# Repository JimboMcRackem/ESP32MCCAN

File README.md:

# ESP32 MCCAN

ESP32 motorcycle lighting controller. It reads the bike's CAN bus and drives 12 on/off outputs.
You configure it from a phone over its own Wi-Fi network.

The firmware is one image. `tools/embed_web.py` embeds the web app from `data/` at build time,
so there is no separate filesystem flash.

Settings and the Wi-Fi password live in NVS (namespace `mccan`). A legacy `/config.json` is
migrated once and then deleted, but only on a unit that still has the old partition table (see
below).

## Flashing over USB

Before the first USB flash of this firmware:

1. `python -m pip install cryptography` (needed by `tools/sign_update.py`).
2. `python tools/sign_update.py keygen`, then commit `src/domain/update_pubkey.h`. Firmware built
   with the all-zero placeholder key refuses every phone update until it is flashed over USB
   again.
3. Export your settings from the app's Backup tab. This firmware uses the `min_spiffs.csv`
   partition table (bigger app slots), so the old `/config.json` is not carried over. Import the
   backup after flashing.

```
PYTHONIOENCODING=utf-8 py -3.13 -m platformio run -e esp32 -t upload
```

This is the only flash. There is no `uploadfs`. Native tests run with `python -m platformio test -e native`.

The controller's Wi-Fi network is `MCCAN-XXXX` (XXXX is the last two bytes of the SoftAP MAC
address, which differs from the base MAC printed on module labels).
The default password is `mccan1234`, and the app nags until you change it.

## Releasing an update

1. Once only, before the first USB flash: `python tools/sign_update.py keygen`. The private key goes to `~/.mccan/update_key.pem`
   and the public half to `src/domain/update_pubkey.h`, which is built into the firmware.
   **Back up the key.** If it is lost, units in the field can only be updated over USB.
2. Bump `kBuildNumber` and `kVersionString` in `src/version.h`.
3. Build: `PYTHONIOENCODING=utf-8 py -3.13 -m platformio run -e esp32`
4. Sign:
   ```
   python tools/sign_update.py sign --key ~/.mccan/update_key.pem --bin .pio/build/esp32/firmware.bin --out mccan-<version>.mcup
   ```

The `.mcup` format is documented at the top of `tools/sign_update.py`.

## Installing an update from the phone

1. Join the `MCCAN-XXXX` network and open the app.
2. Go to the Device tab and choose the `.mcup` file.
3. The controller refuses an older build, and refuses any update while the bike is not parked.
4. After the update it restarts once the bike reads parked. The new image marks itself good
   after it has run for about 5 s with the Wi-Fi network up. If it crashes or is power-cycled
   before that, the next start goes back to the previous image. An image that hangs stays until
   a power cycle, and one that runs but behaves wrongly is kept: install a fixed update.

## Recovering a forgotten password

Factory reset: hold the reset button (GPIO0, labelled BOOT on the dev board) for 10 s while the
controller is running, then **release it within 5 s**. That erases the settings, and the
controller restarts with defaults (password `mccan1234`) as soon as the bike reads parked. A short
press does nothing. If the button is still held 5 s after the 10 s mark, the reset is cancelled;
release it and start a new 10 s hold to try again. The lamps keep working throughout.

Feedback: on the MCCAN board the status LED (GPIO13) fast-blinks at the 10 s mark (release now),
goes solid once the settings are erased, and goes off if cancelled. The dev board has no LED on
GPIO13: watch the serial log instead (`reset button held 10 s: release within 5 s ...`,
`factory reset: settings erased`).

Holding the button at power-up enters the ESP32's USB flashing mode instead. That is harmless.

## Bring-up notes

- On the dev board, a serial terminal that asserts DTR without RTS can hold GPIO0 low through the
  auto-program circuit. Held, it arms the reset at 10 s and cancels it at 15 s; it never erases
  unless the line is released inside that window. Use a monitor that leaves DTR and RTS
  deasserted.
- Hold BOOT through "Connecting......" if the upload cannot connect.

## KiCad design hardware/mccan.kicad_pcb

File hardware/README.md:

# MCCAN Hardware

This is the KiCad 10.0.2 project for the ESP32 MCCAN lighting controller. The board is the
**plan4 board**: 140 × 100 mm, 8 layers, assembled by JLCPCB.

- Schematic spec: `../docs/superpowers/specs/2026-10-17-emarked-module-redesign-design.md`. The
  aux stage has its own spec: `../docs/superpowers/specs/2026-11-13-aux-stage-design.md`.
- Layout spec: `../docs/superpowers/specs/2026-11-13-board-layout-phase-b-design.md`.
- Ordering is in **`docs/fabrication.md`**, the harness in `docs/harness.md`, and routing in
  `docs/routing-tool.md`.

Everything here is generated by `scripts/`. Never hand-edit a `.kicad_sch`, `.kicad_pcb`,
`.kicad_pro` or `.kicad_dru`.

## kicad-cli is not on PATH

Bash:       "/c/Program Files/KiCad/10.0/bin/kicad-cli.exe" <args>
PowerShell: & "C:\Program Files\KiCad\10.0\bin\kicad-cli.exe" <args>

On Windows, set `PYTHONIOENCODING=utf-8`, because several scripts print non-ASCII.

## Board status (phase B, 2026-11-14)

**The board is ready to order.**

- DRC is clean at every severity.
- The JLCPCB package is generated and checked.
- Every BOM line is in stock. U10 relies on owner-approved global sourcing, and L2 (11 in
  stock against 10) is approved for it if it runs short.

See "Last full run" below for the evidence.

- **Outline: 140 × 100 mm, 1 mm corner radius, M3 holes 5 mm in from each corner.**
  - The board fits because the eight wire tails go in one row on the bottom (cable) edge. Their
    courtyards total 122.2 mm, against 123.1 mm between the courtyards of the bottom mounting
    holes.
  - U5 sits on the opposite (top) edge. Its antenna overhangs the edge, and the antenna keep-out
    is clear on every layer.
  - Regions, left to right (`scripts/layout_pcb.py`):
    - feed A input and filter;
    - rails;
    - outputs (U11–U13), with test-pad bank 1;
    - MCU and CAN;
    - feed B and the aux stage (Q13/Q14, U14), with bank 2.
- **Stackup: 8 layers, 1.6 mm, 1 oz on every layer.**
  - Signals run on F.Cu, In2, In5 and B.Cu.
  - GND planes are on In1, In4 and In6, with GND_IN and GND_B islands.
  - In3 is power (VBAT, VBAT_B).
  - Feed B's 6.4 A runs on FEED_B_P pours on F.Cu, In5 and B.Cu.
  - There is no controlled impedance.
- **Assembly:** single-sided, top only, with every part placed by JLCPCB. The only THT parts are
  J2 and L2.
- **J2 (programming header) is fitted by JLCPCB, not left DNP.** L2 needs THT service anyway, and
  bring-up flashes the board over J2. J2 is reachable only with the lid off, as are SW1 and SW2
  beside it. Normal updates go over WiFi (signed OTA).
- **Test pads:** 30 bare SMD pads (TP1–TP30), each labelled with its net name on the silkscreen.
  They are in two banks plus TP30 (GND_IN), and every bank is within clip reach of a GND pad. They
  are not in the BOM.
- **Cables:** one row on the bottom edge, through seven glands (`docs/harness.md` §2).

### Before ordering

1. Re-run the stock check on the day of the order: `python scripts/check_stock.py`. It exits 1 on
   any SHORT or MISSING line. Use `--boards N` for a different quantity.
2. Follow `docs/fabrication.md` §8:
   - confirm **every** row of `output/jlcpcb/rotation-review.txt` (39 parts) in JLCPCB's
     placement preview: no rotation offset has been checked against JLCPCB;
   - read JLCPCB's DFM report.

### Open items

These change values only; the footprints stay.

- **R82–R85**, the yellow series resistors, wait on bench measurements.
- **The blue pod wire (J10.4, J11.4)** is not connected. It waits until its role is measured.
  Keep the pad.
- The fuse ratings and aux circuit ratings must be confirmed on the bike (`docs/harness.md`).

## Verification gates, in run order

Run from `hardware/`, with `K="/c/Program Files/KiCad/10.0/bin/kicad-cli.exe"`:

```
# 1. schematic
python scripts/gen_root.py && python scripts/gen_power_input.py && python scripts/gen_rails.py \
  && python scripts/gen_mcu_can.py && python scripts/gen_outputs.py
"$K" sch export netlist --format kicadsexpr -o output/netlist.net mccan.kicad_sch
"$K" sch erc --severity-error --exit-code-violations -o output/erc.rpt mccan.kicad_sch
python scripts/check_netlist.py

# 2. board (routes come frozen from scripts/routes_signal.json; see docs/routing-tool.md)
python scripts/gen_pcb.py && python scripts/gen_netclasses.py
"$K" pcb drc --severity-all --schematic-parity --refill-zones --exit-code-violations \
  -o output/drc.rpt mccan.kicad_pcb
ok=1; for c in frame placement antenna courtyards grounds zone_islands power_paths \
                plane_width plane_mincut vias geometry; do python scripts/check_$c.py || ok=0; done
python scripts/test_check_plane_mincut.py || ok=0; [ $ok = 1 ]

# 3. fabrication
python scripts/gen_fab.py && python scripts/gen_fab.py --check && python scripts/check_stock.py
```

**DRC must use `--refill-zones`.** Without it, every pad welded to a pour reads as unconnected.

**DRC must run at `--severity-all`.** `--severity-error` discards every rule set to `warning`:
silk, text and library metadata. `gen_netclasses.py` promotes the seven rules that can fail this
board's copper to `error` (`SEVERITIES`). But if a KiCad upgrade adds a rule that defaults to
`warning`, an error-only run would never see it.

The accepted residual is **zero**: 0 violations, 0 unconnected and 0 parity issues, at every
severity. With `--exit-code-violations`, any finding exits 5.

`check_plane_mincut.py` (about a minute) measures each power path's narrowest copper by max-flow
/ min-cut on a 0.1 mm raster, so it finds a neck at any angle. `check_plane_width.py` only cuts
along rows and columns, which can pass a diagonally necked pour; keep it as the fast first look.

`check_density.py` reports how full each region is. It is informational, not a gate.

### Last full run (2026-11-15, robustness changes: U10 ON tie, D25 SMBJ18A, ILIM 56.2 k, J2 silk)

| Step | Result |
|---|---|
| Schematic generators | `power_input` and `outputs` changed as intended; the other sheets byte-identical |
| Netlist diff vs 2026-11-14 | U10.9 joins `VCC10`; D25 SMBJ18A; R62-R64 56.2k; nothing else |
| ERC | 0 violations |
| `check_netlist.py`, `verify_fpmap.py` | every group PASS; 0 failures |
| `gen_pcb.py` | exit 0 (hand routes clear); 2137 frozen segments, 504 router vias, plus the ON track |
| DRC, all severities, parity | **0 violations, 0 unconnected, 0 parity issues** |
| `check_frame`, `placement`, `antenna`, `courtyards`, `grounds`, `zone_islands`, `power_paths`, `plane_width`, `plane_mincut`, `vias`, `geometry`, `test_check_plane_mincut` | PASS |
| `gen_fab.py --check` | PASS: 39 orientation-checked parts (13 recalled, 26 unverified; none confirmed) |
| `check_stock.py --boards 5` | exit 0. U10 (LTC4380) GLOBAL as before (owner-approved); L2 11 for 10 |

## Board setup decisions

**Minimum track width and minimum connection width are both 0.15 mm, and they are tied on
purpose.** `min_connection` is the narrowest copper that may carry a connection. If it were set
above the thinnest legal track, every legitimately necked track would violate a rule that the same
file grants. Only the GND planes may neck further, to 0.12 mm between via antipads, through a
scoped rule in `mccan.kicad_dru` (`scripts/gen_netclasses.py`, `PLANE_NECK_RULE`).

**Reference designators are on F.Fab, except J\*, F\*, U\*, Q\*, D\* and L\*.**

- Test pads are identified on the silkscreen by their **net name** instead (`gen_pcb.tp_labels`).
- `gen_pcb.silk_refs` places each kept designator clear of every pad, of every other part's silk,
  of its own outline and of the board edge.
- Values are on F.Fab, so `output/jlcpcb/assembly.pdf` is a fully labelled copy.

## Sheet responsibilities

| Sheet | Contents |
|---|---|
| power_input | Feed A (J1): LTC4380 U10 surge stopper with Q10/Q11 (no board fuse; the fuse is in the harness), 24 V TVS, pi + CM filter -> `VBAT`. Feed B (J9): SQJ461EP P-FET Q13 for reverse polarity, 15 V gate zener D24, SMBJ18A TVS D25 (29.2 V clamp, inside U14's 35 V) -> `VBAT_B`, no filter, no LTC4380. `GND_B` (also the pods' return, out to the outputs sheet) meets `GND_IN` (the connector side of choke L2) only at net-tie NT1, so neither feed's return current bypasses L2's return winding |
| rails | Low-Iq buck -> `+3V3_ALW`, gated `+5V` (`EN_5V`). No boost and no `+3V3_SW` |
| mcu_can | ESP32-WROOM-32E, TJA1042T/3 (listen-only, TXD pulled up, no MCU link), programming header, 4.7 k series resistors on the diagnostic lines. GPIO 13 is `AUX_PWM` (left pod yellow; the status LED is gone, 2026-11-13) and GPIO 12 is `AUX_PWM_R` (right pod yellow, 2026-11-21) |
| outputs | Three TPS4HC120A-Q1 quads U11-U13 (TPS4H160B until 2026-11-13, no stock) (D1: 12 channels, 10 used, 2 spare), harness tails J3 (front, 5), J4 + J5 (rear, 4 + 3), CAN tail J8. Aux stage (2026-11-13): BTS7008-2EPA U14 switches both pods from `VBAT_B`, 74AHCT1G126GV U15 (left) buffers `AUX_PWM` and U16 (right) buffers `AUX_PWM_R` to its yellow (enabled only while that pod is powered), pod tails J10/J11. See `docs/superpowers/specs/2026-11-13-aux-stage-design.md` |

The pin map and net names are the generators' (`scripts/gen_*.py`, `scripts/quadpins.py`) and the
netlist `output/netlist.net`. The plan3 pin tables that used to be here (PCA9685, mux, ignition
sense, PWM nets) described a board that no longer exists and have been removed.

### ESP32 pin rules that still hold

- GPIO 6-11 are the module's flash and are unusable. GPIO 37 and 38 are not bonded out.
- GPIO 34-39 are input-only and have **no internal pulls**. Here: 34 `SNS_A`, 35 `CAN_RXD`
  (RTC, EXT1 wake), 36 `SNS_B`, 39 `SNS_C`.
- ADC2 fails while Wi-Fi is up, so the sense inputs are all ADC1.
- Strapping pins, and what this board ties them to:
  - GPIO 0 is `BOOT_N`: the BOOT button SW1 and the auto-reset transistor Q3.
  - GPIO 2 is `DIAG_EN`: 4.7 k series, with R33 47 k pull-down on the chip side. It must be low
    for download, and the same pull-down holds the switches' `DIAG_EN` low. High level: 47 k ∥ 33.3 k
    (three chips at 100 k min) = 19.5 k, so 3.3 × 19.5 / (19.5 + 4.7) = 2.66 V against VIH 2.0 V.
  - GPIO 5 and 15 are `DIAG_SEL0` / `DIAG_SEL1`: 4.7 k series, **no pull** (their level is
    irrelevant while `DIAG_EN` is low). The three SEH internal pull-downs (100 k min each) load
    GPIO 15 against its internal pull-up, so the ROM boot log will probably be muted; that is
    harmless. Optional fix: a 10 k pull-up on the MCU side of R32 (not fitted).
  - GPIO 12 is `AUX_PWM_R`, the right pod's yellow PWM to U16 (2026-11-21), with R36 10 k to GND
    (flash voltage select, and the buffer input's pull-down). It is also the firmware's nominal TWAI
    TX pin: `CanBus::begin` hands it back to input + pull-down once TWAI starts, and only then does
    the firmware attach the right pod's LEDC channel. It must never be driven high through a reset.
- No lamp output sits on a strapping pin or on GPIO 14.

### Layout notes (honoured by the plan4 layout)

- **U10 (LTC4380) `ON` is tied to `VCC10`** (2026-11-15). It used to be left open on its internal
  1 Mohm pull-up, which needs < 1 uA leakage to ground: about 400 kOhm of moisture or flux would
  have held the whole board off. A 0.15 mm F.Cu track runs from pad 9 under the body to `VCC10`'s
  via. The old In1 keep-out and `check_power_paths` guard stay as belt-and-braces.
- `NT1` is the deliberate `GND_B` / `GND_IN` star point (connector side of L2, so no return current bypasses L2's return winding); place it deliberately (spec §4.1.1). It is a 2.0 mm tie so it outlasts the harness fuse when one feed is reversed while the other is connected.

### Bring-up checklist

- **ROM boot log may be absent.** The three SEH internal pull-downs load GPIO 15 (MTDO), so the boot ROM log is probably muted. Harmless. Optional fix: a 10 k pull-up on the MCU side of R32 (not fitted).
- **GPIO12 / flash voltage.** The TWAI driver needs a TX pin and drives it high; on this board that is GPIO12, the MTDI strap. Since 2026-11-15 `CanBus::begin` returns GPIO12 to input + pull-down right after `twai_start()` (listen-only never transmits), and R36 holds it low at every reset. Since 2026-11-21 GPIO12 is also `AUX_PWM_R`, the right pod's yellow PWM, attached only after `CanBus::begin`. Check on the bench: GPIO12 reads ~0 V while running with the right pod off, carries the pod PWM when it is on, and CAN frames still arrive. The optional permanent remedy is `espefuse.py set_flash_voltage 3.3V`, which is **IRREVERSIBLE** and is the owner's decision; it has not been run.
- **Diagnostics settling.** After any `DIAG_SEL` or `DIAG_EN` change wait >= 400 us before reading `SNS_x`.
- **Reverse polarity.** Test one feed reversed with the other disconnected, and the whole harness reversed. Test one feed reversed with the other connected only on a current-limited bench supply: that drives fault current through NT1 and the shared return until the harness fuse clears.
- `R100` (33 mOhm) sets feed A's limit at 1.36-1.67 A, between its ~0.87 A load and its ~2 A fuse (aux spec A10). Re-check it against the measured start-up current.
- **Shorted lamp vs feed A's limit.** The quads' ILIM is 0.25 A (R62-R64 56.2 k, since 2026-11-15; was 0.5 A). The MCU's rail is behind U10, so one short at 0.5 A (peaking 1.4x) on top of the 0.87 A worst case could reach U10's limit and reset the MCU in a loop. At 0.25 A a single short stays under it (~1.24 A) and that channel latches off. Check on a current-limited bench supply: with all lamps on, short one output to GND; the board must stay up and only that channel go dark. Two simultaneous shorts can still trip U10.
- **J2 is not an FTDI header.** Pin order 3V3 GND TX RX DTR RTS (labelled on the silk). A generic FTDI cable (GND CTS VCC TX RX RTS) puts GND on +3V3_ALW and 5 V on TXD0. Use the MCCAN programmer.

Plan3 history (the 200 × 140 mm PCBWay board, the RGB output stage, Task 1 status) is in git history and `archive/`.

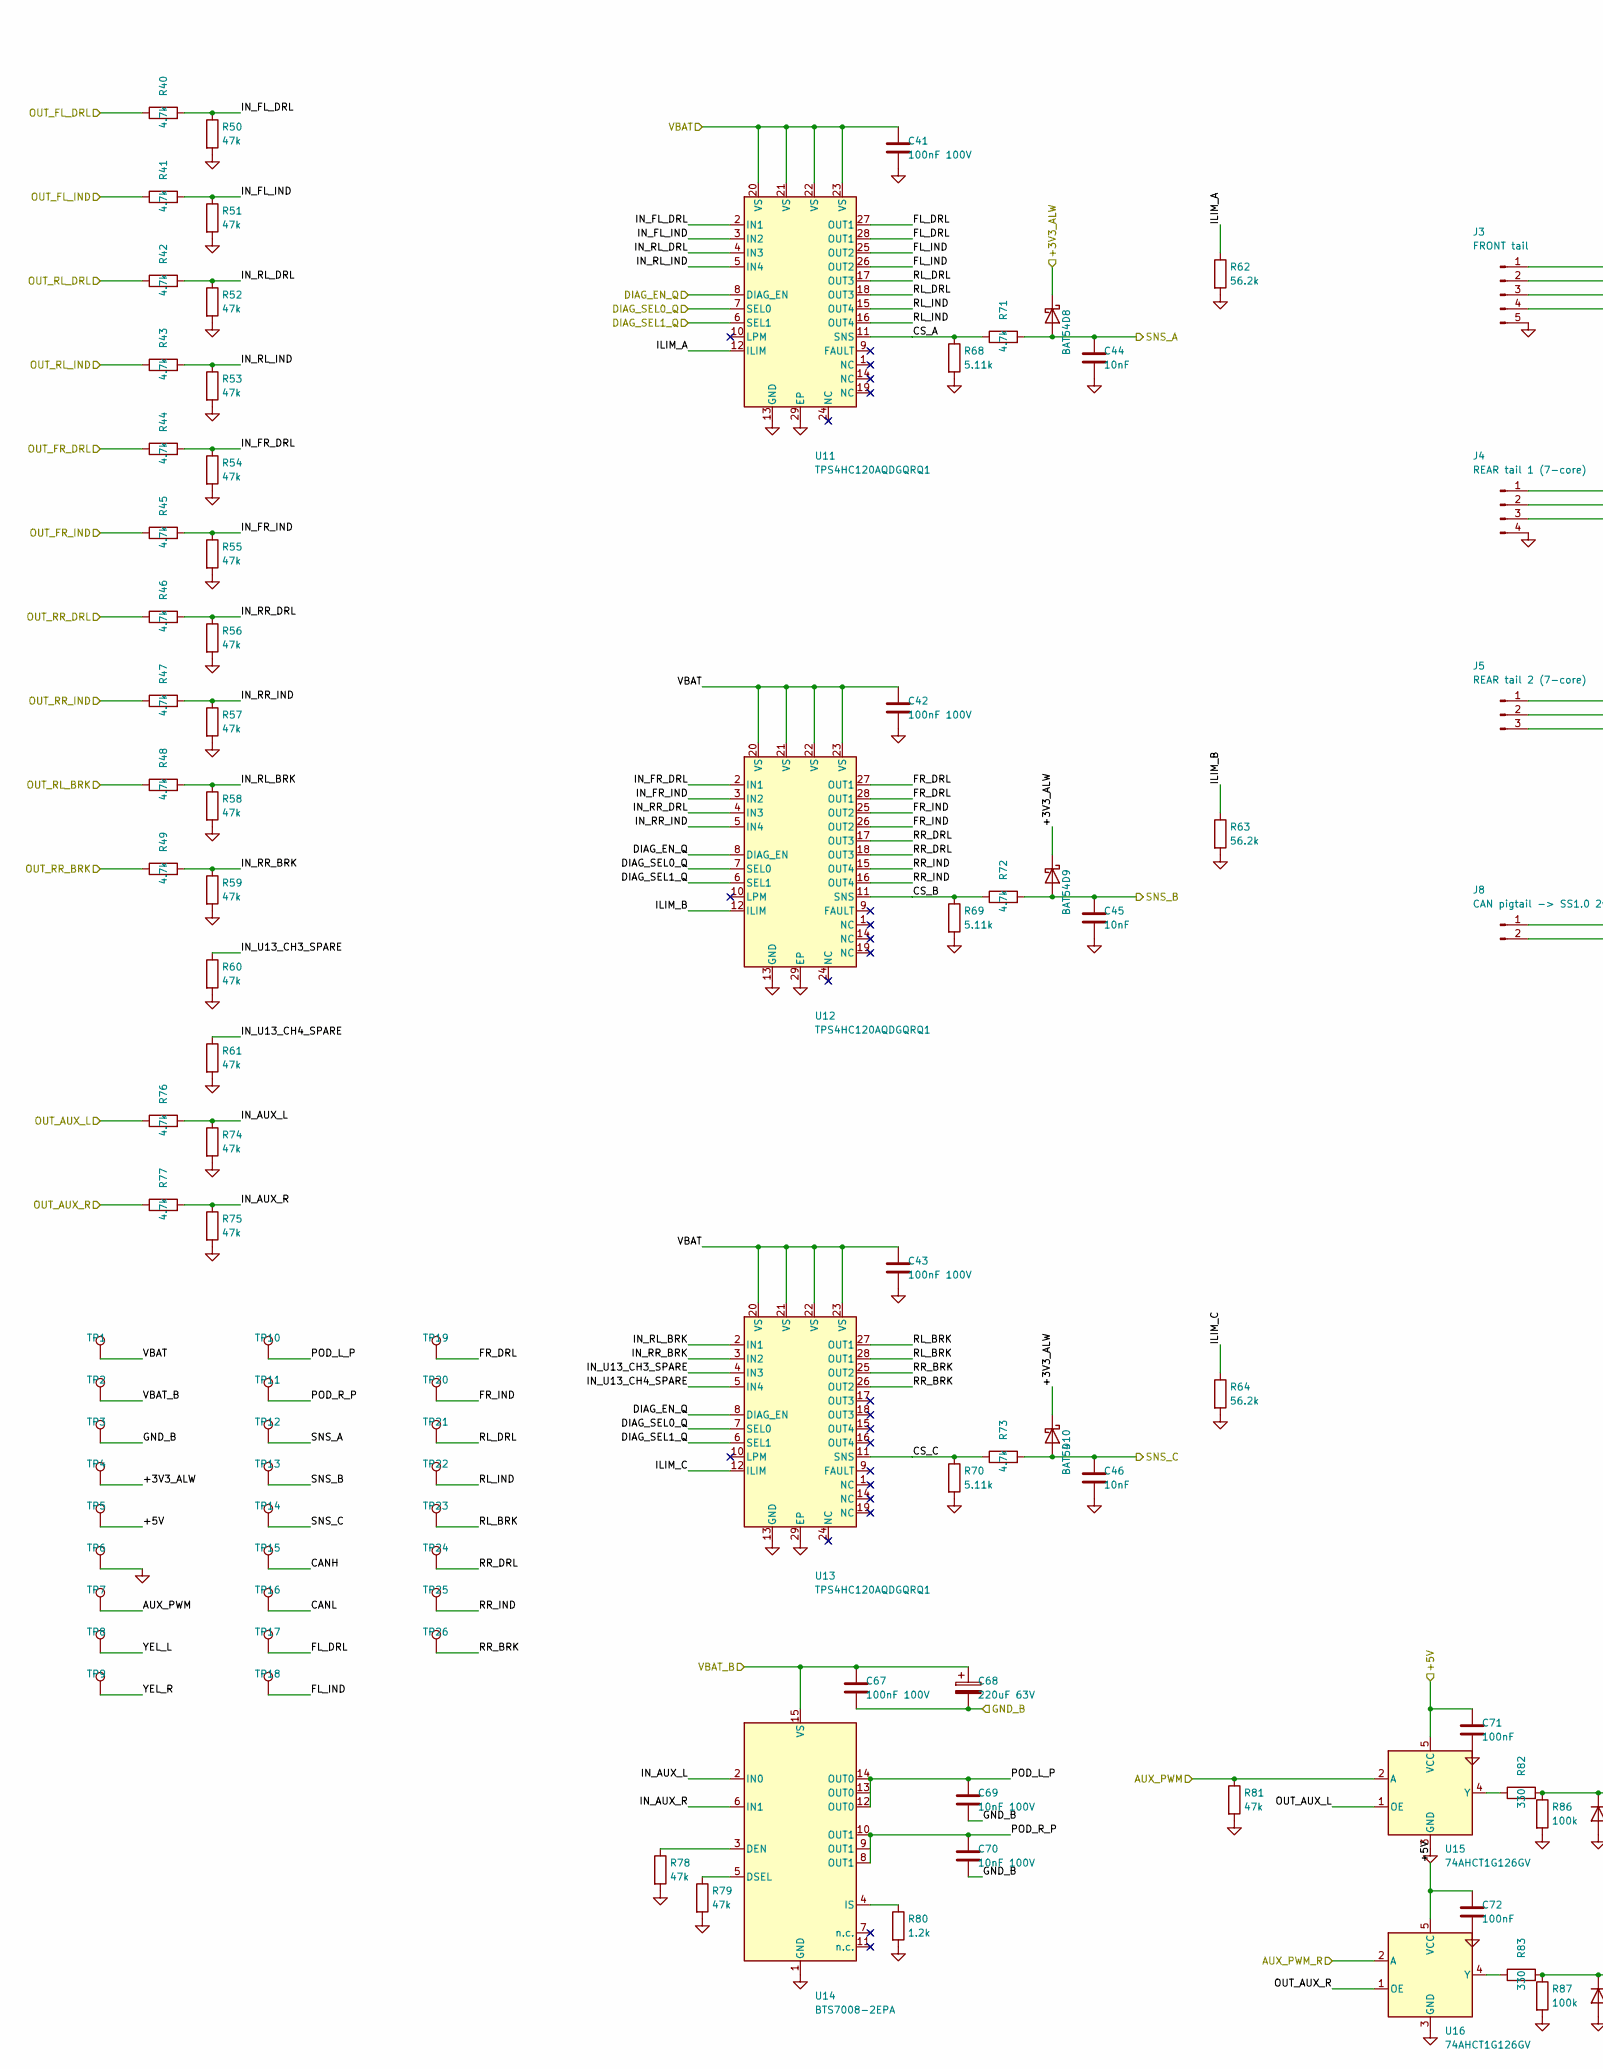
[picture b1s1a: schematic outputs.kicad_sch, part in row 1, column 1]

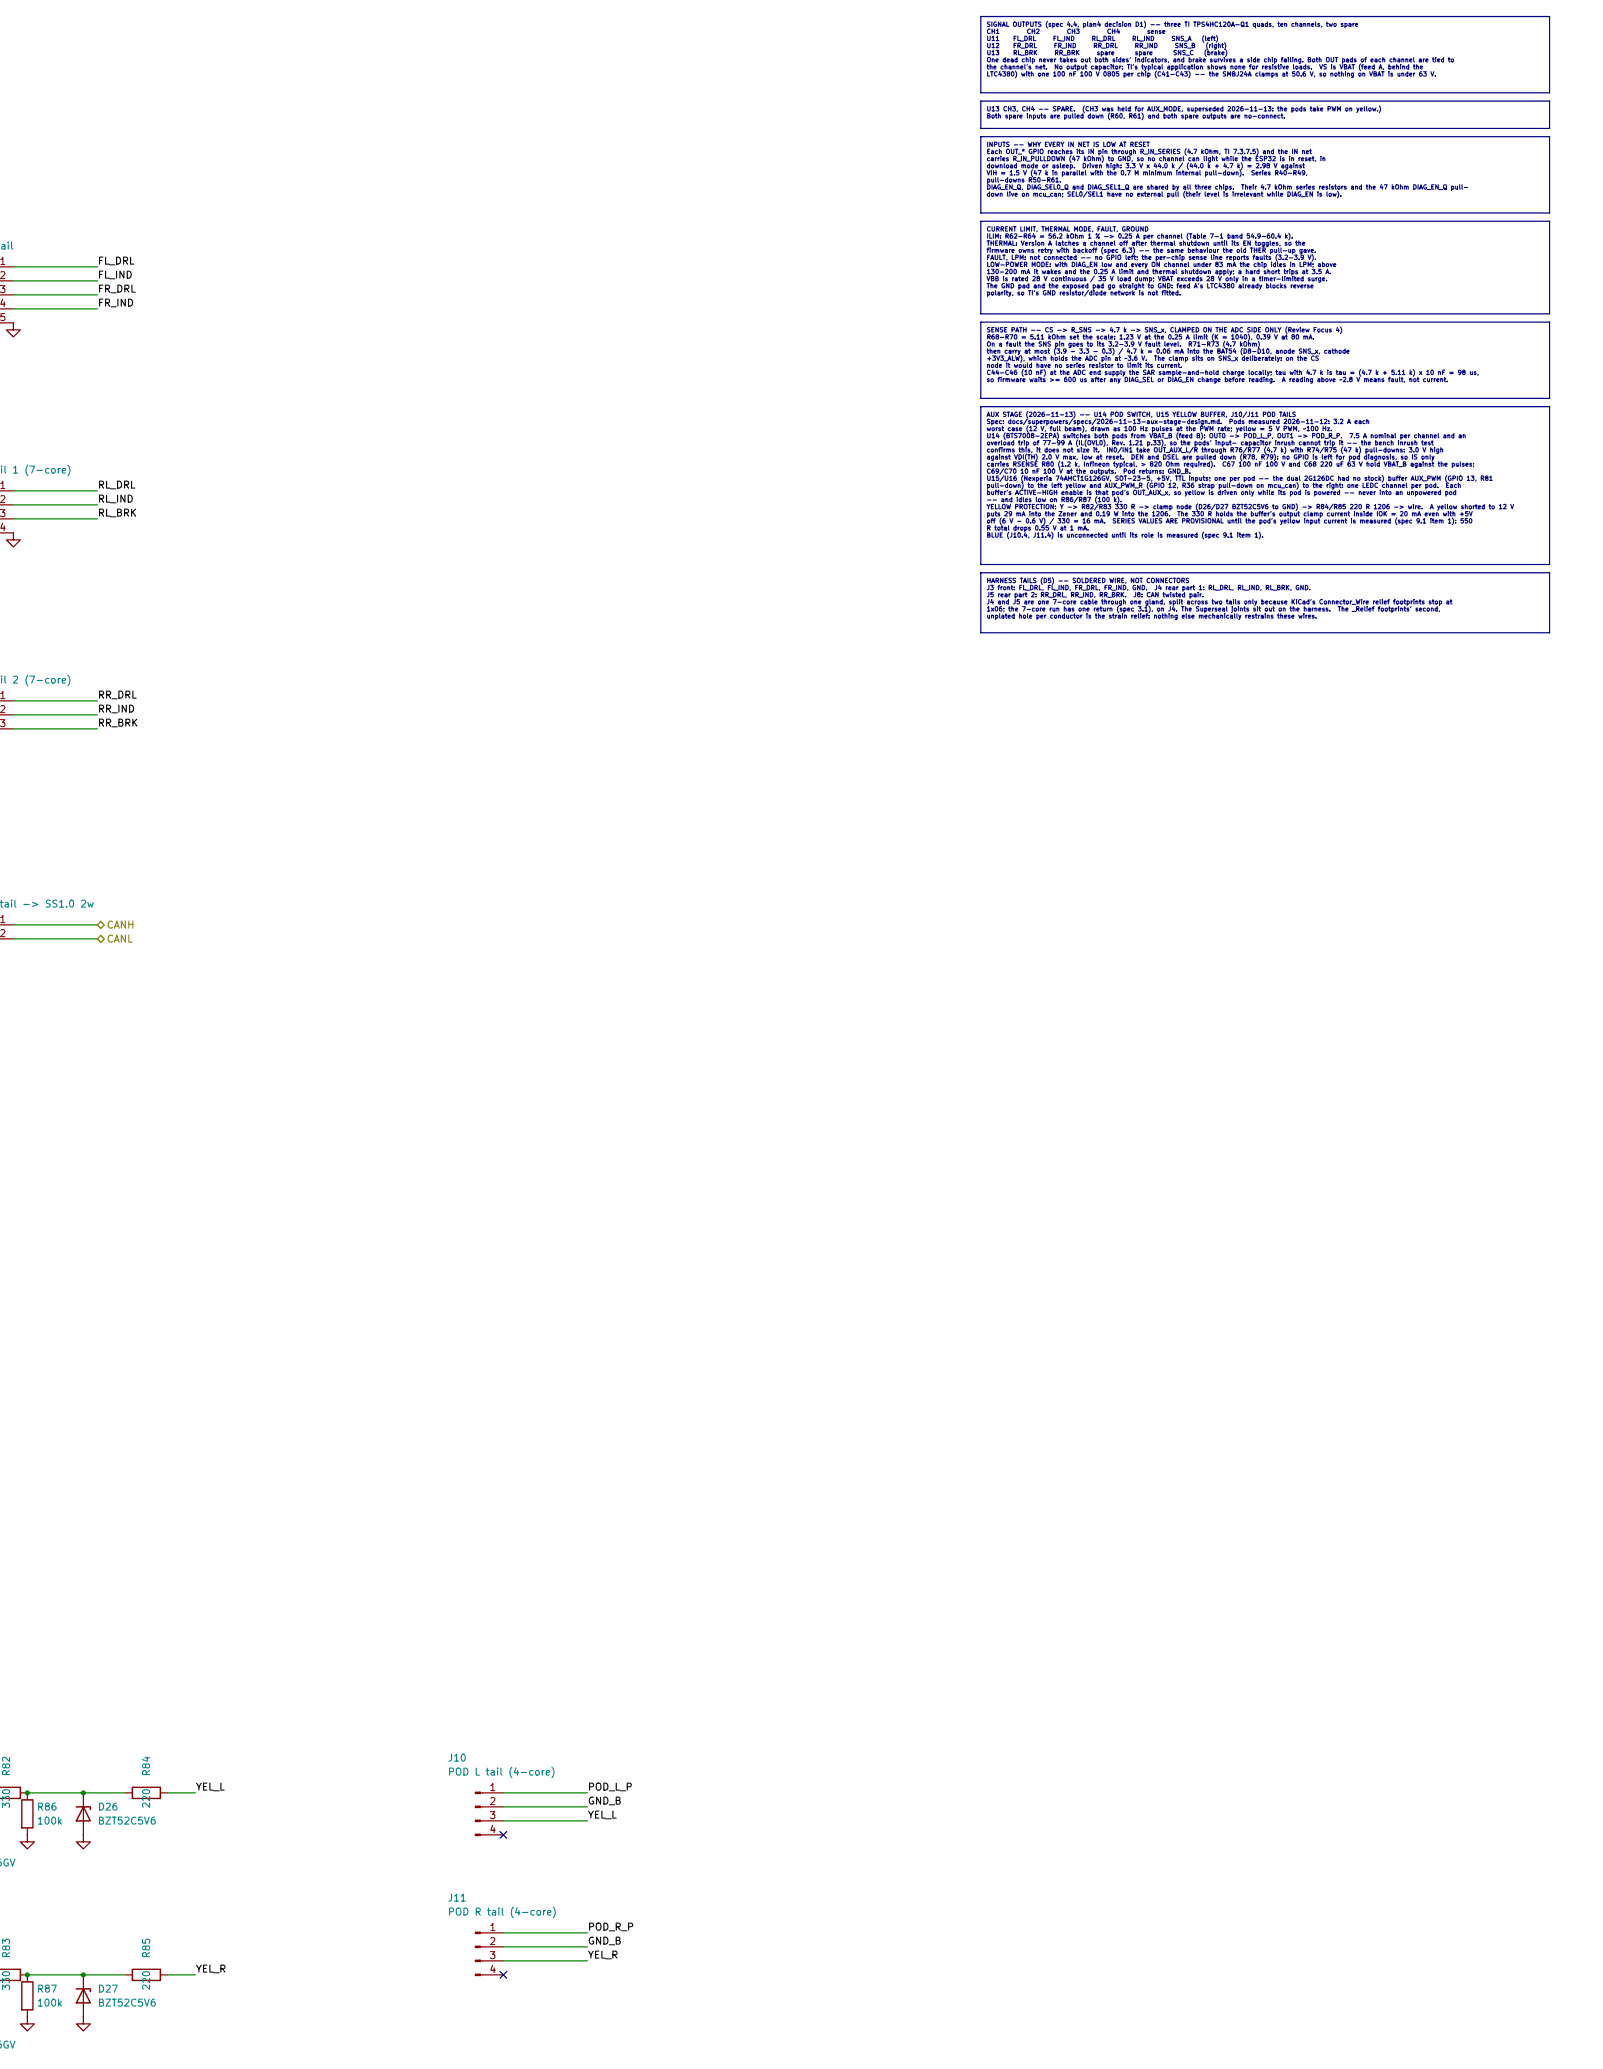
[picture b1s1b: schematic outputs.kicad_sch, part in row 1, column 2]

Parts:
C41, C42, C43, C67: 100nF 100V; C_0805_2012Metric
C44, C45, C46: 10nF; C_0603_1608Metric
C68: 220uF 63V; CP_Elec_10x10.5
C69, C70: 10nF 100V; C_0805_2012Metric
C71, C72: 100nF; C_0603_1608Metric
D8, D9, D10: BAT54; D_SOD-123
D26, D27: BZT52C5V6; D_SOD-123
J3: FRONT tail; SolderWire-0.5sqmm_1x05_P4.6mm_D0.9mm_OD2.1mm_Relief
J4: REAR tail 1 (7-core); SolderWire-0.5sqmm_1x04_P4.6mm_D0.9mm_OD2.1mm_Relief
J5: REAR tail 2 (7-core); SolderWire-0.5sqmm_1x03_P4.6mm_D0.9mm_OD2.1mm_Relief
J8: CAN pigtail -> SS1.0 2w; SolderWire-0.5sqmm_1x02_P4.6mm_D0.9mm_OD2.1mm_Relief
J10: POD L tail (4-core); SolderWire-1sqmm_1x04_P5.4mm_D1.4mm_OD2.7mm_Relief
J11: POD R tail (4-core); SolderWire-1sqmm_1x04_P5.4mm_D1.4mm_OD2.7mm_Relief
R40, R41, R42, R43, R44, R45, R46, R47, R48, R49, R71, R72, R73, R76, R77: 4.7k; R_0603_1608Metric
R50, R51, R52, R53, R54, R55, R56, R57, R58, R59, R60, R61, R74, R75, R78, R79, R81: 47k; R_0603_1608Metric
R62, R63, R64: 56.2k; R_0603_1608Metric
R68, R69, R70: 5.11k; R_0603_1608Metric
R80: 1.2k; R_0603_1608Metric
R82, R83: 330; R_0603_1608Metric
R84, R85: 220; R_1206_3216Metric
R86, R87: 100k; R_0603_1608Metric
TP1: VBAT; TestPoint_Pad_D1.5mm
TP2: VBAT_B; TestPoint_Pad_D1.5mm
TP3: GND_B; TestPoint_Pad_D1.5mm
TP4: +3V3_ALW; TestPoint_Pad_D1.5mm
TP5: +5V; TestPoint_Pad_D1.5mm
TP6: GND; TestPoint_Pad_D1.5mm
TP7: AUX_PWM; TestPoint_Pad_D1.5mm
TP8: YEL_L; TestPoint_Pad_D1.5mm
TP9: YEL_R; TestPoint_Pad_D1.5mm
TP10: POD_L_P; TestPoint_Pad_D1.5mm
TP11: POD_R_P; TestPoint_Pad_D1.5mm
TP12: SNS_A; TestPoint_Pad_D1.5mm
TP13: SNS_B; TestPoint_Pad_D1.5mm
TP14: SNS_C; TestPoint_Pad_D1.5mm
TP15: CANH; TestPoint_Pad_D1.5mm
TP16: CANL; TestPoint_Pad_D1.5mm
TP17: FL_DRL; TestPoint_Pad_D1.5mm
TP18: FL_IND; TestPoint_Pad_D1.5mm
TP19: FR_DRL; TestPoint_Pad_D1.5mm
TP20: FR_IND; TestPoint_Pad_D1.5mm
TP21: RL_DRL; TestPoint_Pad_D1.5mm
TP22: RL_IND; TestPoint_Pad_D1.5mm
TP23: RL_BRK; TestPoint_Pad_D1.5mm
TP24: RR_DRL; TestPoint_Pad_D1.5mm
TP25: RR_IND; TestPoint_Pad_D1.5mm
TP26: RR_BRK; TestPoint_Pad_D1.5mm
U11, U12, U13: TPS4HC120AQDGQRQ1; TI_DGQ0028C
U14: BTS7008-2EPA; Infineon_PG-TSDSO-14-22
U15, U16: 74AHCT1G126GV; SOT-23-5

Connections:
/+3V3_ALW: D8.1 (K), D9.1 (K), D10.1 (K), TP4.1; also elsewhere on the board
/+5V: C71.1, C72.1, TP5.1, U15.5 (VCC), U16.5 (VCC); also elsewhere on the board
/AUX_PWM: R81.1, TP7.1, U15.2 (A); also elsewhere on the board
/AUX_PWM_R: U16.2 (A); also elsewhere on the board
/CANH: J8.1, TP15.1; also elsewhere on the board
/CANL: J8.2, TP16.1; also elsewhere on the board
/DIAG_EN_Q: U11.8 (DIAG_EN), U12.8 (DIAG_EN), U13.8 (DIAG_EN); also elsewhere on the board
/DIAG_SEL0_Q: U11.7 (SEL0), U12.7 (SEL0), U13.7 (SEL0); also elsewhere on the board
/DIAG_SEL1_Q: U11.6 (SEL1), U12.6 (SEL1), U13.6 (SEL1); also elsewhere on the board
/GND_B: C67.2, C68.2, C69.2, C70.2, J10.2, J11.2, TP3.1; also elsewhere on the board
/OUT_AUX_L: R76.1, U15.1 (OE); also elsewhere on the board
/OUT_AUX_R: R77.1, U16.1 (OE); also elsewhere on the board
/OUT_FL_DRL: R40.1; also elsewhere on the board
/OUT_FL_IND: R41.1; also elsewhere on the board
/OUT_FR_DRL: R44.1; also elsewhere on the board
/OUT_FR_IND: R45.1; also elsewhere on the board
/OUT_RL_BRK: R48.1; also elsewhere on the board
/OUT_RL_DRL: R42.1; also elsewhere on the board
/OUT_RL_IND: R43.1; also elsewhere on the board
/OUT_RR_BRK: R49.1; also elsewhere on the board
/OUT_RR_DRL: R46.1; also elsewhere on the board
/OUT_RR_IND: R47.1; also elsewhere on the board
/SNS_A: C44.1, D8.2 (A), R71.2, TP12.1; also elsewhere on the board
/SNS_B: C45.1, D9.2 (A), R72.2, TP13.1; also elsewhere on the board
/SNS_C: C46.1, D10.2 (A), R73.2, TP14.1; also elsewhere on the board
/VBAT: C41.1, C42.1, C43.1, TP1.1, U11.20 (VS), U11.21 (VS), U11.22 (VS), U11.23 (VS), U12.20 (VS), U12.21 (VS), U12.22 (VS), U12.23 (VS), U13.20 (VS), U13.21 (VS), U13.22 (VS), U13.23 (VS); also elsewhere on the board
/VBAT_B: C67.1, C68.1, TP2.1, U14.15 (VS); also elsewhere on the board
/outputs/CS_A: R68.1, R71.1, U11.11 (SNS)
/outputs/CS_B: R69.1, R72.1, U12.11 (SNS)
/outputs/CS_C: R70.1, R73.1, U13.11 (SNS)
/outputs/FL_DRL: J3.1, TP17.1, U11.27 (OUT1), U11.28 (OUT1)
/outputs/FL_IND: J3.2, TP18.1, U11.25 (OUT2), U11.26 (OUT2)
/outputs/FR_DRL: J3.3, TP19.1, U12.27 (OUT1), U12.28 (OUT1)
/outputs/FR_IND: J3.4, TP20.1, U12.25 (OUT2), U12.26 (OUT2)
/outputs/ILIM_A: R62.1, U11.12 (ILIM)
/outputs/ILIM_B: R63.1, U12.12 (ILIM)
/outputs/ILIM_C: R64.1, U13.12 (ILIM)
/outputs/IN_AUX_L: R74.1, R76.2, U14.2 (IN0)
/outputs/IN_AUX_R: R75.1, R77.2, U14.6 (IN1)
/outputs/IN_FL_DRL: R40.2, R50.1, U11.2 (IN1)
/outputs/IN_FL_IND: R41.2, R51.1, U11.3 (IN2)
/outputs/IN_FR_DRL: R44.2, R54.1, U12.2 (IN1)
/outputs/IN_FR_IND: R45.2, R55.1, U12.3 (IN2)
/outputs/IN_RL_BRK: R48.2, R58.1, U13.2 (IN1)
/outputs/IN_RL_DRL: R42.2, R52.1, U11.4 (IN3)
/outputs/IN_RL_IND: R43.2, R53.1, U11.5 (IN4)
/outputs/IN_RR_BRK: R49.2, R59.1, U13.3 (IN2)
/outputs/IN_RR_DRL: R46.2, R56.1, U12.4 (IN3)
/outputs/IN_RR_IND: R47.2, R57.1, U12.5 (IN4)
/outputs/IN_U13_CH3_SPARE: R60.1, U13.4 (IN3)
/outputs/IN_U13_CH4_SPARE: R61.1, U13.5 (IN4)
/outputs/POD_L_P: C69.1, J10.1, TP10.1, U14.12 (OUT0), U14.13 (OUT0), U14.14 (OUT0)
/outputs/POD_R_P: C70.1, J11.1, TP11.1, U14.8 (OUT1), U14.9 (OUT1), U14.10 (OUT1)
/outputs/RL_BRK: J4.3, TP23.1, U13.27 (OUT1), U13.28 (OUT1)
/outputs/RL_DRL: J4.1, TP21.1, U11.17 (OUT3), U11.18 (OUT3)
/outputs/RL_IND: J4.2, TP22.1, U11.15 (OUT4), U11.16 (OUT4)
/outputs/RR_BRK: J5.3, TP26.1, U13.25 (OUT2), U13.26 (OUT2)
/outputs/RR_DRL: J5.1, TP24.1, U12.17 (OUT3), U12.18 (OUT3)
/outputs/RR_IND: J5.2, TP25.1, U12.15 (OUT4), U12.16 (OUT4)
/outputs/YEL_L: J10.3, R84.2, TP8.1
/outputs/YEL_R: J11.3, R85.2, TP9.1
GND: C41.2, C42.2, C43.2, C44.2, C45.2, C46.2, C71.2, C72.2, D26.2 (A), D27.2 (A), J3.5, J4.4, R50.2, R51.2, R52.2, R53.2, R54.2, R55.2, R56.2, R57.2, R58.2, R59.2, R60.2, R61.2, R62.2, R63.2, R64.2, R68.2, R69.2, R70.2, R74.2, R75.2, R78.2, R79.2, R80.2, R81.2, R86.2, R87.2, TP6.1, U11.13 (GND), U11.29 (EP), U12.13 (GND), U12.29 (EP), U13.13 (GND), U13.29 (EP), U14.1 (GND), U15.3 (GND), U16.3 (GND); also elsewhere on the board
unnamed: D26.1 (K), R82.2, R84.1, R86.1
unnamed: D27.1 (K), R83.2, R85.1, R87.1
unnamed: R78.1, U14.3 (DEN)
unnamed: R79.1, U14.5 (DSEL)
unnamed: R80.1, U14.4 (IS)
unnamed: R82.1, U15.4 (Y)
unnamed: R83.1, U16.4 (Y)

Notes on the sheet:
SENSE PATH -- CS -> R_SNS -> 4.7 k -> SNS_x, CLAMPED ON THE ADC SIDE ONLY (Review Focus 4) R68-R70 = 5.11 kOhm set the scale: 1.23 V at the 0.25 A limit (K = 1040), 0.39 V at 80 mA. On a fault the SNS pin goes to its 3.2-3.9 V fault level. R71-R73 (4.7 kOhm) then carry at most (3.9 - 3.3 - 0.3) / 4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
CURRENT LIMIT, THERMAL MODE, FAULT, GROUND ILIM: R62-R64 = 56.2 kOhm 1 % -> 0.25 A per channel (Table 7-1 band 54.9-60.4 k). THERMAL: Version A latches a channel off after thermal shutdown until its EN toggles, so the firmware owns retry with backoff (spec 6.3) -- the same behaviour the old THER pu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
AUX STAGE (2026-11-13) -- U14 POD SWITCH, U15 YELLOW BUFFER, J10/J11 POD TAILS Spec: docs/superpowers/specs/2026-11-13-aux-stage-design.md. Pods measured 2026-11-12: 3.2 A each worst case (12 V, full beam), drawn as 100 Hz pulses at the PWM rate; yellow = 5 V PWM, ~100 Hz. U14 (BTS7008-2EPA) switch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
HARNESS TAILS (D5) -- SOLDERED WIRE, NOT CONNECTORS J3 front: FL_DRL, FL_IND, FR_DRL, FR_IND, GND. J4 rear part 1: RL_DRL, RL_IND, RL_BRK, GND. J5 rear part 2: RR_DRL, RR_IND, RR_BRK. J8: CAN twisted pair. J4 and J5 are one 7-core cable through one gland, split across two tails only because KiCad's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
U13 CH3, CH4 -- SPARE. (CH3 was held for AUX_MODE, superseded 2026-11-13: the pods take PWM on yellow.) Both spare inputs are pulled down (R60, R61) and both spare outputs are no-connect.
SIGNAL OUTPUTS (spec 4.4, plan4 decision D1) -- three TI TPS4HC120A-Q1 quads, ten channels, two spare CH1 CH2 CH3 CH4 sense U11 FL_DRL FL_IND RL_DRL RL_IND SNS_A (left) U12 FR_DRL FR_IND RR_DRL RR_IND SNS_B (right) U13 RL_BRK RR_BRK spare spare SNS_C (brake) One dead chip never takes out both sides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
INPUTS -- WHY EVERY IN NET IS LOW AT RESET Each OUT_* GPIO reaches its IN pin through R_IN_SERIES (4.7 kOhm, TI 7.3.7.5) and the IN net carries R_IN_PULLDOWN (47 kOhm) to GND, so no channel can light while the ESP32 is in reset, in download mode or asleep. Driven high: 3.3 V x 44.0 k / (44.0 k + 4.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
